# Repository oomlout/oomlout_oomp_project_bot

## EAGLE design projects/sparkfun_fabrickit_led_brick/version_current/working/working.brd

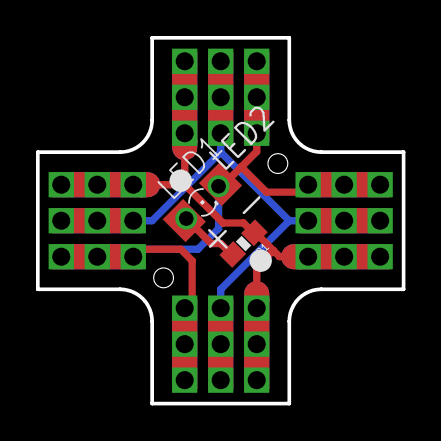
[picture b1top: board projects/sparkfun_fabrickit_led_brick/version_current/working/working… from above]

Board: 2 copper layers, 20.3 x 20.3 mm, 8 parts (0 on the bottom side), 4 nets.

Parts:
J1, J2: FKIT-RIBBON_CONNECTOR-2MM_L_REV2; FKIT-RIBBON_CONNECTOR_03_2MM_L
J3, J4: FKIT-RIBBON_CONNECTOR-2MM_R_REV2; FKIT-RIBBON_CONNECTOR_03_2MM_R
LED1: FKIT-LED-1206_NO_CREAM
LED2: LED3MM-NS
R1: 0603-RES
U$1: CREATIVE_COMMONS

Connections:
5V: J1.P1A, J2.P1A, J3.P1A, J4.P1A, R1.1
GND: J1.P3A, J2.P3A, J3.P3A, J4.P3A, LED1.C, LED2.K
unnamed: J1.P2A, J2.P2A, J3.P2A, J4.P2A
unnamed: LED1.A, LED2.A, R1.2

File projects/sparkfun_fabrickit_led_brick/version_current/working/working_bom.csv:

Row,Description,Part,References,Value,Footprint,Quantity Per PCB,Status,Datasheet
1,,FKIT-RIBBON_CONNECTOR-2MM_L_REV2,J1 J2,FKIT-RIBBON_CONNECTOR-2MM_L_REV2,FKIT-RIBBON_CONNECTOR_03_2MM_L,2, ,
2,,FKIT-RIBBON_CONNECTOR-2MM_R_REV2,J3 J4,FKIT-RIBBON_CONNECTOR-2MM_R_REV2,FKIT-RIBBON_CONNECTOR_03_2MM_R,2, ,
3,,LED,LED1,LED,FKIT-LED-1206_NO_CREAM,1, ,
4,,LED-3MM-NO_SILK,LED2,LED-3MM-NO_SILK,LED3MM-NS,1, ,
5,,RESISTOR0603,R1,RESISTOR0603,0603-RES,1, ,
6,,CREATIVE_COMMONS,U$1,CREATIVE_COMMONS,CREATIVE_COMMONS,1, ,





Project info:
Schematic:,working
Variant:,default
Revision:,
Date:,2023-08-06_12-56-02
KiCad Version:,7.0.6-7.0.6~ubuntu22.04.1
Statistics:
Component Groups:,6
Component Count:,8 (0 SMD/ 0 THT)
Fitted Components:,8 (0 SMD/ 0 THT)
Number of PCBs:,1
Total Components:,8

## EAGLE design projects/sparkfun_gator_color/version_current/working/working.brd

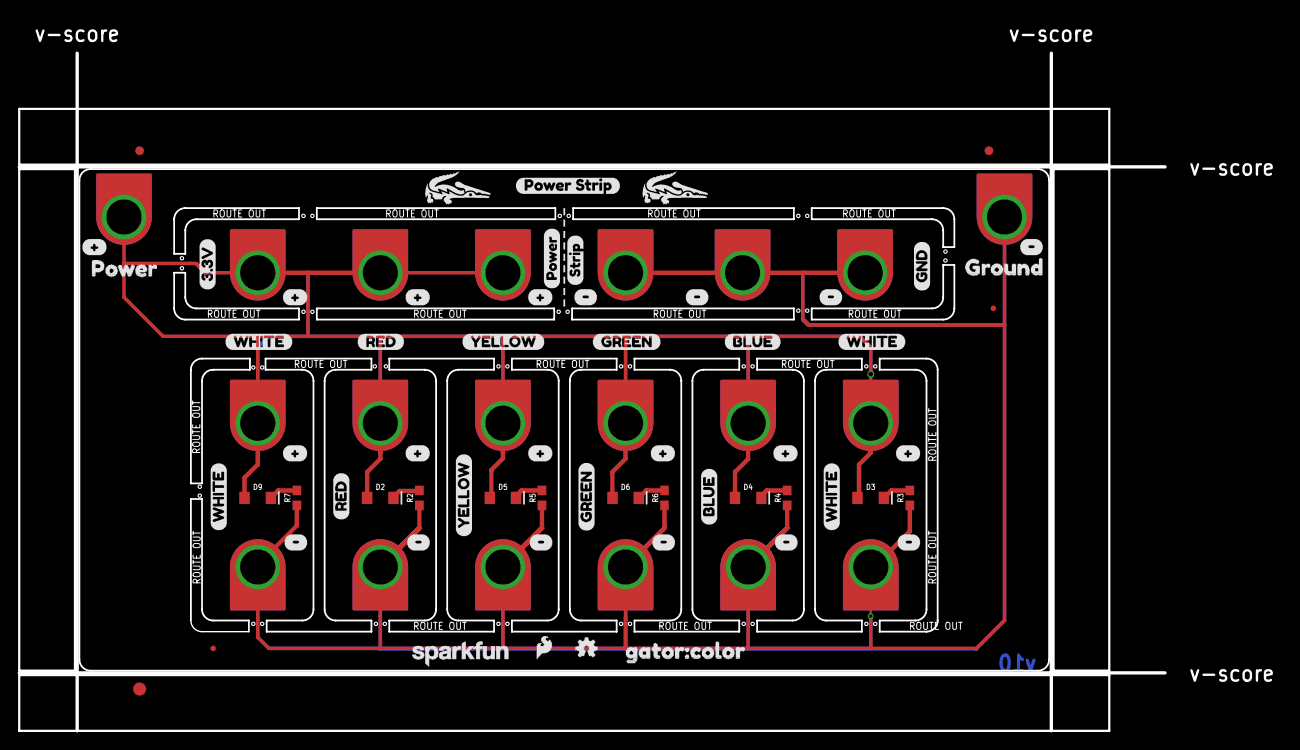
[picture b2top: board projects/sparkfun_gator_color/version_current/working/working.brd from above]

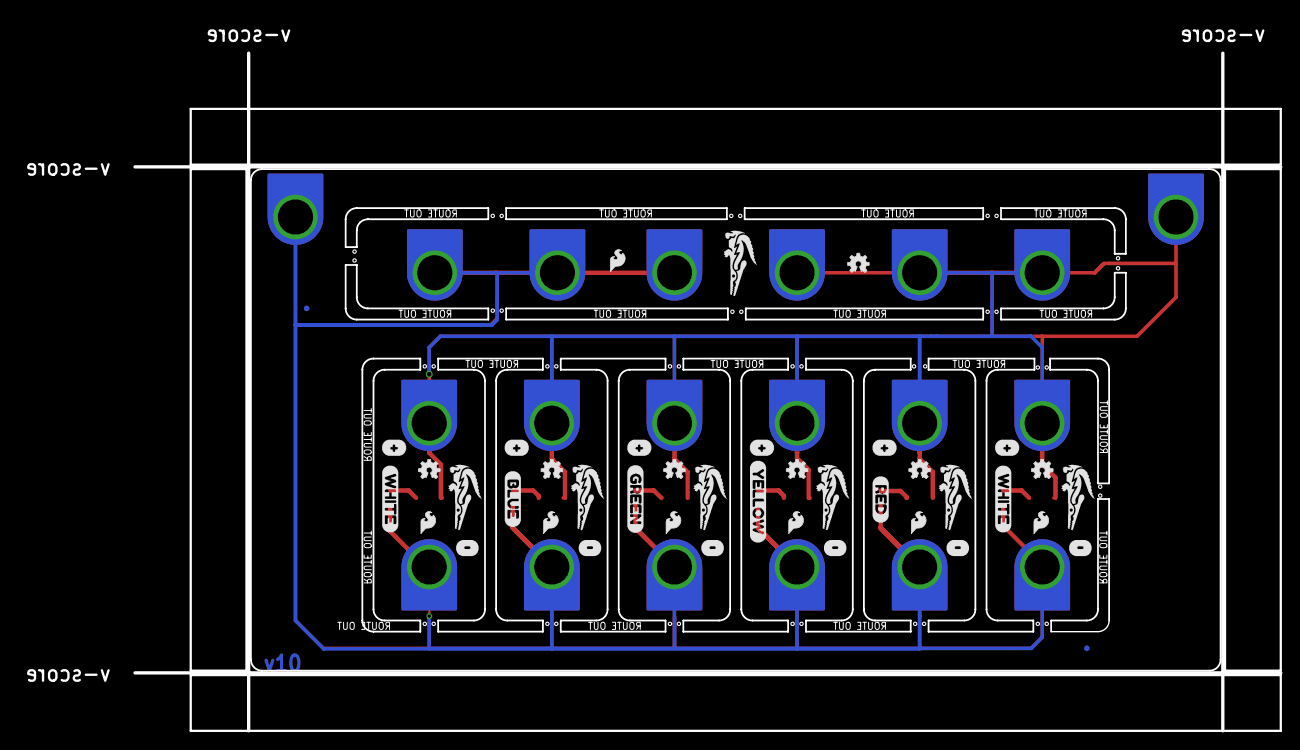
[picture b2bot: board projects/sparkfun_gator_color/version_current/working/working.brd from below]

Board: 2 copper layers, 130.6 x 77.2 mm, 123 parts (41 on the bottom side), 8 nets.

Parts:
D2: RED; LED-1206
D3, D9: WHITE; LED-1206
D4: BLUE; LED-1206
D5: Yellow; LED-1206
D6: GREEN; LED-1206
E$1, E$2: FIDUCIAL-1X2
E$3: FIDUCIAL-1.5X3
FD1, FD2, FD3, FD4: FIDUCIALUFIDUCIAL; FIDUCIAL-MICRO
LOGO1, LOGO9, LOGO10, LOGO11, LOGO12, LOGO13, LOGO17, LOGO19: SFE_LOGO_FLAME.1_INCH; SFE_LOGO_FLAME_.1
LOGO2, LOGO3, LOGO4, LOGO5, LOGO6, LOGO7, LOGO15, LOGO18: OSHW-LOGOMINI; OSHW-LOGO-MINI
LOGO16: SFE_LOGO_NAME.1_INCH; SFE_LOGO_NAME_.1
R2, R3, R5, R7: 330; 0603
R4, R6: 150; 0603
U$1, U$2, U$3, U$6, U$7, U$8, U$10, U$11, U$13, U$16, U$18, U$19, U$20, U$21, U$28, U$30, U$32, U$33, U$34, U$38: TAB_GATOR_MINI
U$5: POWER_STRIP0
U$9: GROUND3
U$12, U$14, U$15, U$53, U$55, U$57, U$60, U$62, U$64, U$77, U$81, U$83, U$84, U$85, U$86, U$87: #8
U$17, U$41, U$42: RED2
U$22, U$23, U$24, U$54, U$56, U$58, U$61, U$63, U$65, U$82, U$89, U$90, U$91, U$92, U$93, U$95: #9
U$25: 3#3V1
U$26: GND0
U$27: POWER1
U$29, U$31, U$50, U$68, U$69, U$70, U$71, U$72, U$73: GATOR#PNG
U$35: STRIP2
U$36, U$37, U$75: BLUE4
U$39, U$40, U$67: GREEN3
U$43: POWER2
U$44, U$45, U$46, U$47, U$78, U$79: WHITE6
U$48, U$49, U$76: YELLOW5
U$51: GATOR#COLOR0

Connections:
3.3V: D2.A, D3.A, D4.A, D5.A, D6.A, D9.A, U$10.P1, U$13.P1, U$16.P1, U$18.P1, U$19.P1, U$20.P1, U$21.P1, U$32.P1, U$33.P1, U$34.P1
GND: R2.1, R3.1, R4.1, R5.1, R6.1, R7.1, U$1.P1, U$2.P1, U$3.P1, U$6.P1, U$7.P1, U$8.P1, U$11.P1, U$28.P1, U$30.P1, U$38.P1
unnamed: D2.C, R2.2
unnamed: D3.C, R3.2
unnamed: D4.C, R4.2
unnamed: D5.C, R5.2
unnamed: D6.C, R6.2
unnamed: D9.C, R7.2

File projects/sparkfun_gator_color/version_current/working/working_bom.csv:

Row,Description,Part,References,Value,Footprint,Quantity Per PCB,Status,Datasheet
1,,LED-BLUE1206,D4,BLUE,LED-1206,1, ,
2,,LED-GREEN1206,D6,GREEN,LED-1206,1, ,
3,,LED-RED1206,D2,RED,LED-1206,1, ,
4,,LED-WHITE1206,D3 D9,WHITE,LED-1206,2, ,
5,,LED-YELLOWLILYPAD,D5,Yellow,LED-1206,1, ,
6,,FRAME-LETTER,FRAME1,FRAME-LETTER,CREATIVE_COMMONS,1, ,
7,,OSHW-LOGOMINI,LOGO2 LOGO15,OSHW-LOGOMINI,OSHW-LOGO-MINI,2, ,
8,,REVISION,LOGO8,REVISION,REVISION,1, ,
9,,SFE_LOGO_FLAME.1_INCH,LOGO1,SFE_LOGO_FLAME.1_INCH,SFE_LOGO_FLAME_.1,1, ,
10,,SFE_LOGO_NAME.1_INCH,LOGO16,SFE_LOGO_NAME.1_INCH,SFE_LOGO_NAME_.1,1, ,
11,,150OHM-0603-1/10W-1%,R4 R6,150OHM-0603-1/10W-1%,0603,2, ,
12,,330OHM-0603-1/10W-1%,R2 R3 R5 R7,330OHM-0603-1/10W-1%,0603,4, ,
13,,TAB_GATOR_MINI,U$1 U$2 U$3 U$6 U$7 U$8 U$10 U$11 U$13 U$16 U$18 U$19 U$20 U$21 U$28 U$30 U$32 U$33 U$34 U$38,TAB_GATOR_MINI,TAB_GATOR_MINI,20, ,





Project info:
Schematic:,working
Variant:,default
Revision:,
Date:,2023-08-06_12-56-02
KiCad Version:,7.0.6-7.0.6~ubuntu22.04.1
Statistics:
Component Groups:,13
Component Count:,38 (0 SMD/ 0 THT)
Fitted Components:,38 (0 SMD/ 0 THT)
Number of PCBs:,1
Total Components:,38

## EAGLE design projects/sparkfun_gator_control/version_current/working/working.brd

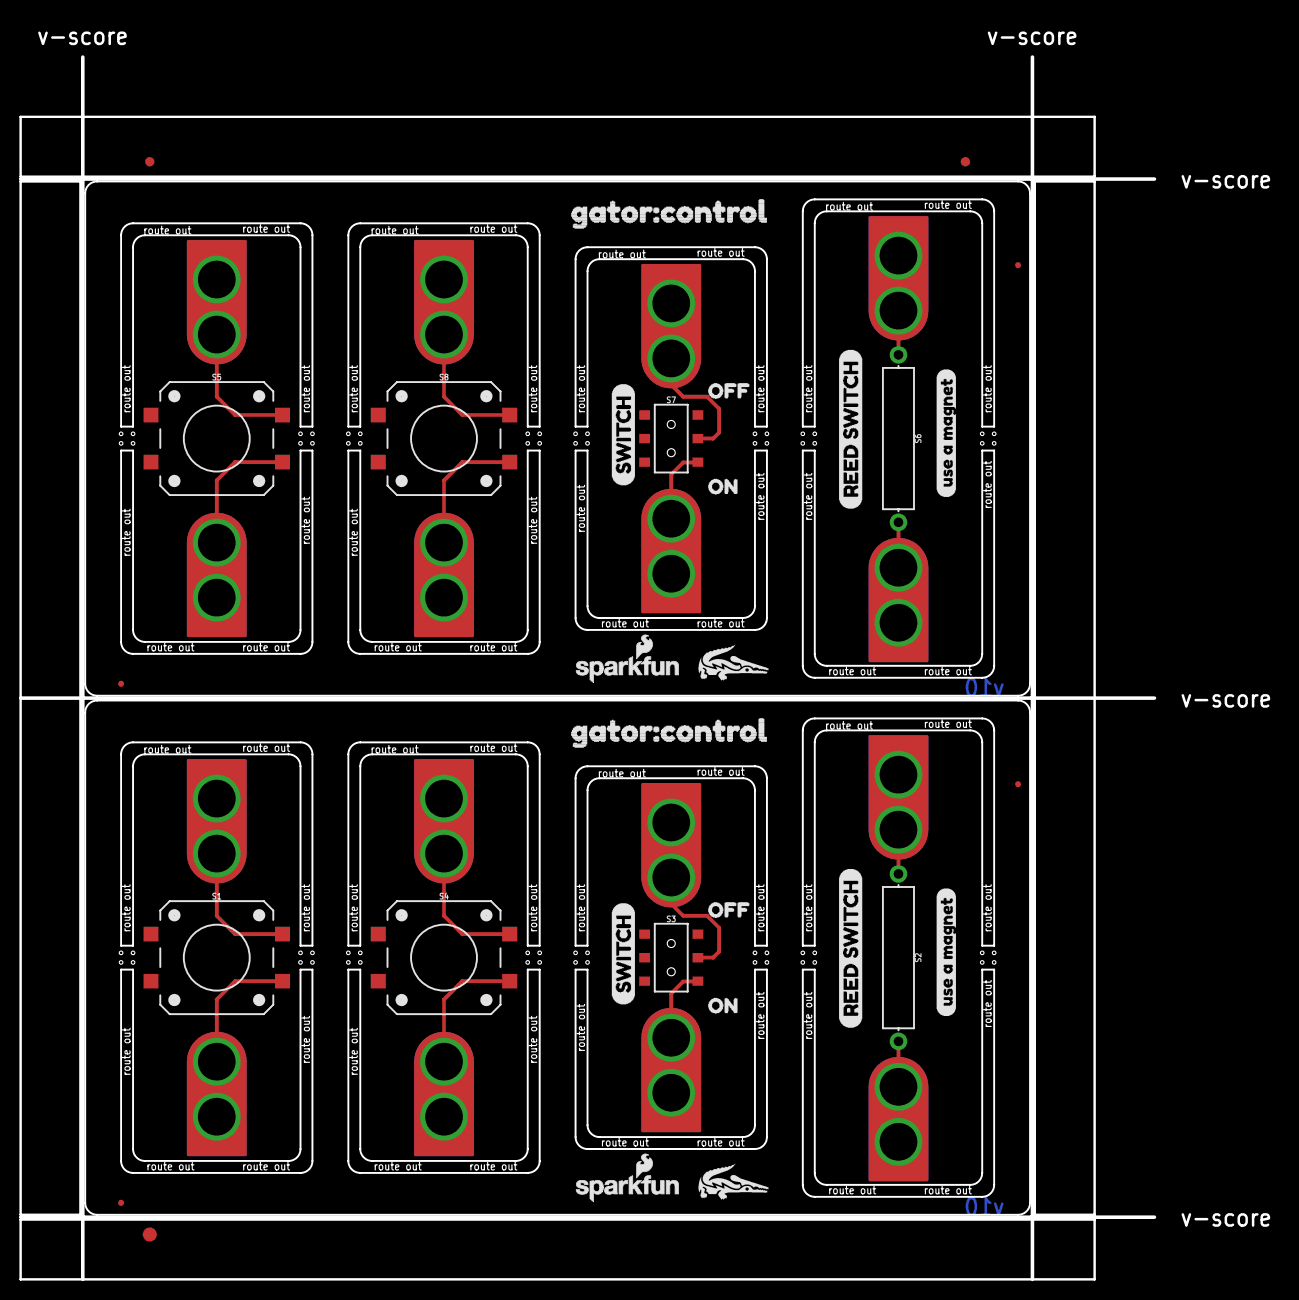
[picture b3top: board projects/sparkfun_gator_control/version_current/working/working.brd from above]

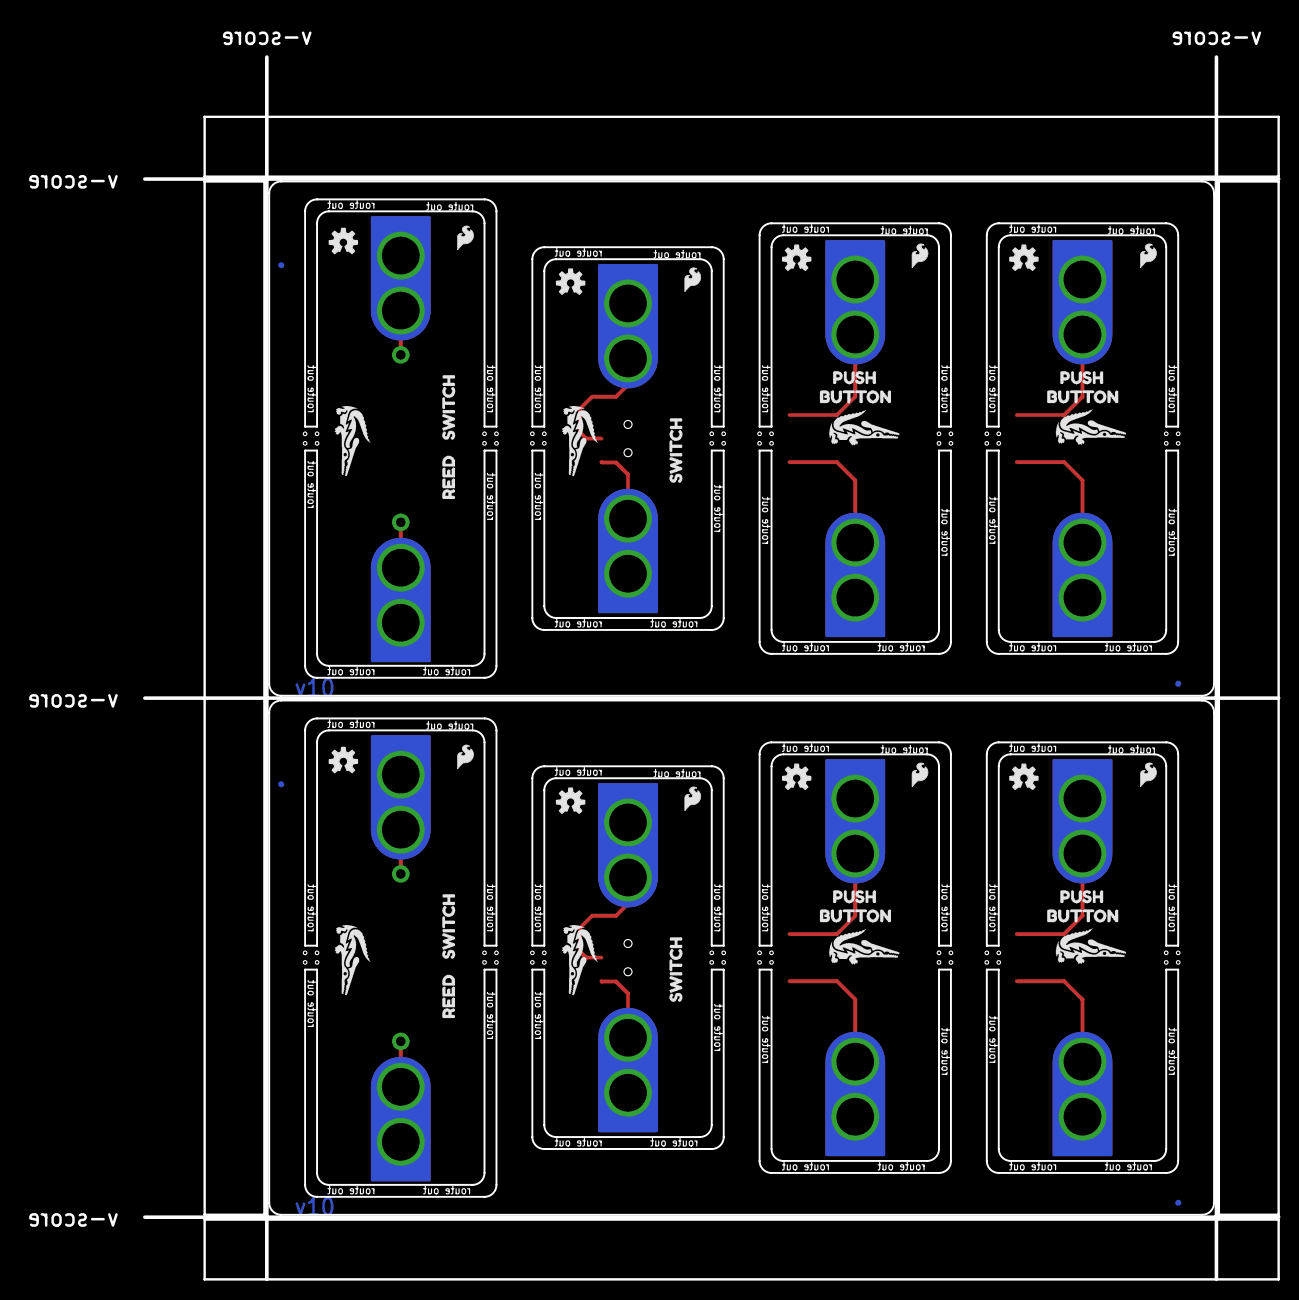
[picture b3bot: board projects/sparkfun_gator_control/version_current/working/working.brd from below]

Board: 2 copper layers, 120.4 x 129.8 mm, 89 parts (42 on the bottom side), 16 nets.

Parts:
E$1, E$2: FIDUCIAL-1X2
E$3: FIDUCIAL-1.5X3
FD1, FD2, FD3, FD4, FD5, FD6, FD7, FD8: FIDUCIALUFIDUCIAL; FIDUCIAL-MICRO
LOGO1, LOGO4, LOGO6, LOGO7, LOGO9, LOGO12, LOGO14, LOGO15: SFE_LOGO_FLAME.1_INCH; SFE_LOGO_FLAME_.1
LOGO2, LOGO3, LOGO5, LOGO8, LOGO10, LOGO11, LOGO13, LOGO16: OSHW-LOGOS; OSHW-LOGO-S
S1, S4, S5, S8: MOMENTARY-SWITCH-SPST-SMD-12MM; TACTILE_SWITCH_SMD_12MM
S2, S6: REED_SWITCH-PTH-INSULATED; REED_SWITCH_PLASTIC
S3, S7: SWITCH_DPDT_SMD_AYZ0202
U$1, U$22, U$25, U$26, U$27, U$28, U$29, U$38, U$51, U$70: GATOR#PNG
U$2, U$5, U$39, U$42: BUTTON3
U$3, U$4, U$40, U$41: PUSH4
U$6, U$46: OFF9
U$7, U$43: REED_SWITCH0
U$8, U$44: SWITCH2
U$9, U$45: USE_A_MAGNET10
U$10, U$11, U$12, U$14, U$15, U$16, U$17, U$19, U$30, U$31, U$32, U$33, U$34, U$35, U$36, U$37: GATOR
U$13, U$47: ON8
U$18, U$21, U$48, U$50: SWITCH5
U$20, U$49: REED6
U$23, U$52: GATOR#CONTROL0
U$24, U$53: SFE_LOGO_NAME_FLAME_.1

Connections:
unnamed: S4.1, U$19.P$1, U$19.P$2
unnamed: S4.3, U$10.P$1, U$10.P$2
unnamed: S1.1, U$17.P$1, U$17.P$2
unnamed: S1.3, U$11.P$1, U$11.P$2
unnamed: S2.P$1, U$16.P$1, U$16.P$2
unnamed: S2.P$2, U$12.P$1, U$12.P$2
unnamed: S3.2, U$15.P$1, U$15.P$2
unnamed: S3.3, U$14.P$1, U$14.P$2
unnamed: S8.1, U$37.P$1, U$37.P$2
unnamed: S8.3, U$30.P$1, U$30.P$2
unnamed: S5.1, U$36.P$1, U$36.P$2
unnamed: S5.3, U$31.P$1, U$31.P$2
unnamed: S6.P$1, U$35.P$1, U$35.P$2
unnamed: S6.P$2, U$32.P$1, U$32.P$2
unnamed: S7.2, U$34.P$1, U$34.P$2
unnamed: S7.3, U$33.P$1, U$33.P$2

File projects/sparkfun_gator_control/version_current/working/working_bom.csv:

Row,Description,Part,References,Value,Footprint,Quantity Per PCB,Status,Datasheet
1,,FRAME-LETTER,FRAME1,FRAME-LETTER,CREATIVE_COMMONS,1, ,
2,,OSHW-LOGOS,LOGO2,OSHW-LOGOS,OSHW-LOGO-S,1, ,
3,,REVISION,LOGO9,REVISION,REVISION,1, ,
4,,SFE_LOGO_FLAME.1_INCH,LOGO1,SFE_LOGO_FLAME.1_INCH,SFE_LOGO_FLAME_.1,1, ,
5,,MOMENTARY-SWITCH-SPST-SMD-12MM,S1 S4,MOMENTARY-SWITCH-SPST-SMD-12MM,TACTILE_SWITCH_SMD_12MM,2, ,
6,,REED_SWITCH-PTH-INSULATED,S2,REED_SWITCH-PTH-INSULATED,REED_SWITCH_PLASTIC,1, ,
7,,SWITCH-SPDT-SMD-AYZ0202,S3,SWITCH-SPDT-SMD-AYZ0202,SWITCH_DPDT_SMD_AYZ0202,1, ,
8,,GATOR,U$10 U$11 U$12 U$14 U$15 U$16 U$17 U$19,GATOR,GATOR,8, ,





Project info:
Schematic:,working
Variant:,default
Revision:,
Date:,2023-08-06_12-56-02
KiCad Version:,7.0.6-7.0.6~ubuntu22.04.1
Statistics:
Component Groups:,8
Component Count:,16 (0 SMD/ 0 THT)
Fitted Components:,16 (0 SMD/ 0 THT)
Number of PCBs:,1
Total Components:,16

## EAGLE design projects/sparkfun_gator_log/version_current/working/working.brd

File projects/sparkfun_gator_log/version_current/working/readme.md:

# OOMP Project  
## gator_log  by sparkfun  
  
oomp key: oomp_projects_flat_sparkfun_gator_log  
(snippet of original readme)  
  
SparkFun gator:log - micro:bit Accessory Board  
========================================  

[*SparkFun gator:log - micro:bit Accessory Board (DEV-15270)*](https://www.sparkfun.com/products/15270)  
  
The gator:log is the perfect data logging tool for your next experiment. With the automation of the data collection process, gone are the days of rushing around with a pen and composition notebook to simultaneously record data and your observations. The gator:log allows a student(s) to focus more on what is happening in the experiment than watching a thermometer or sensor readout.  
  
Instead of using pin connections or requiring soldering, this product provides connection pads for a more kid freindly experience with alligator clips. The design intention of this product is to be used with the [gato:bit (v2)](https://www.sparkfun.com/products/15162), and the [micro:bit development board](https://www.sparkfun.com/products/14208).  
  
Repository Contents  
-------------------  
  
* **/Firmware/Qwiic_OpenLog** - The core sketch that runs Qwiic OpenLog  
* **/Hardware** - Eagle design files (.brd, .sch)  
  
Documentation  
--------------  
  
* **[Hookup Guide](https://learn.sparkfun.com/tutorials/sparkfun-gatorlog-hookup-guide)** - Basic hookup guide for the gator:log.  
* **[gator:RTC PXT Package](https://github.com/sparkfun/pxt-gator-log)** - PXT- packa  
  full source readme at [readme_src.md](readme_src.md)  
  
source repo at: [https://github.com/sparkfun/gator_log](https://github.com/sparkfun/gator_log)  
## Board  

## Schematic  

[schematic pdf](working_schematic.pdf)  
## Images

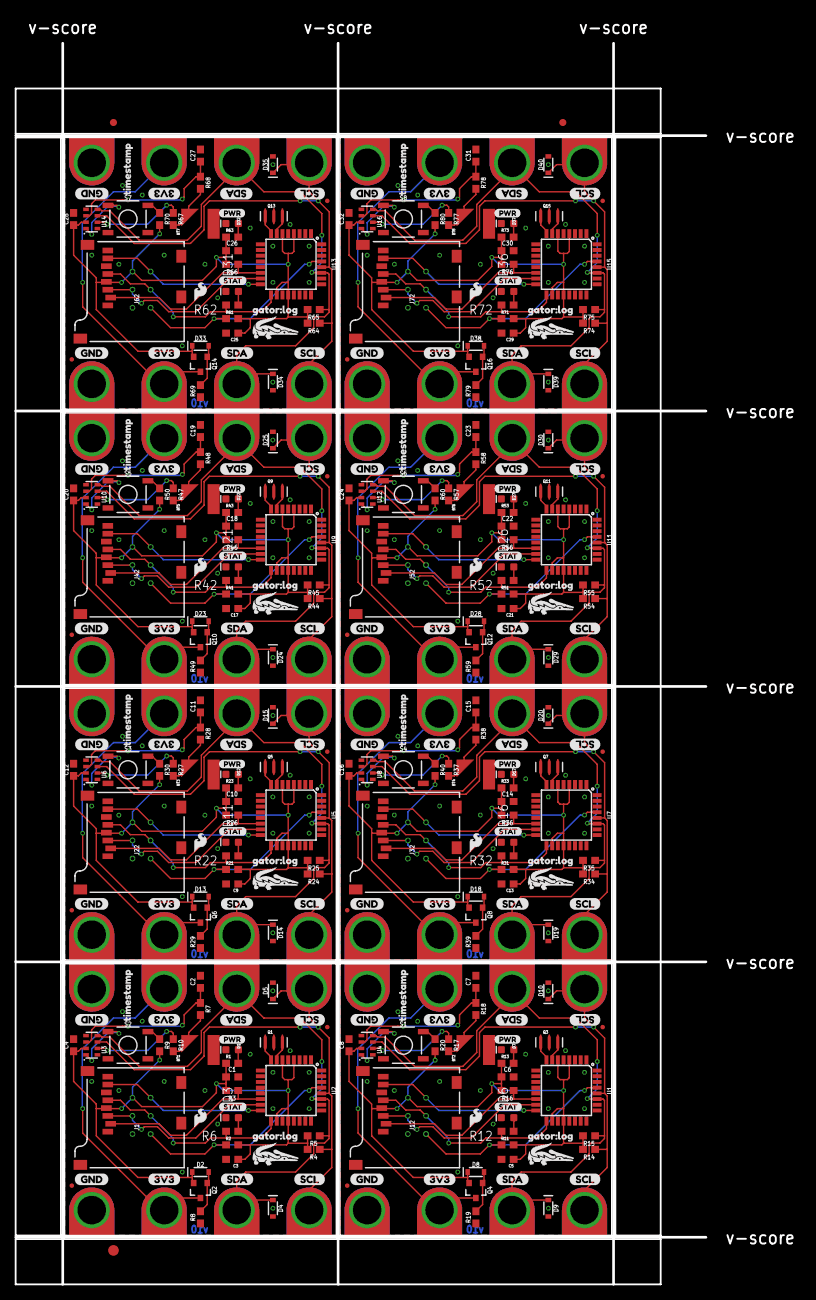
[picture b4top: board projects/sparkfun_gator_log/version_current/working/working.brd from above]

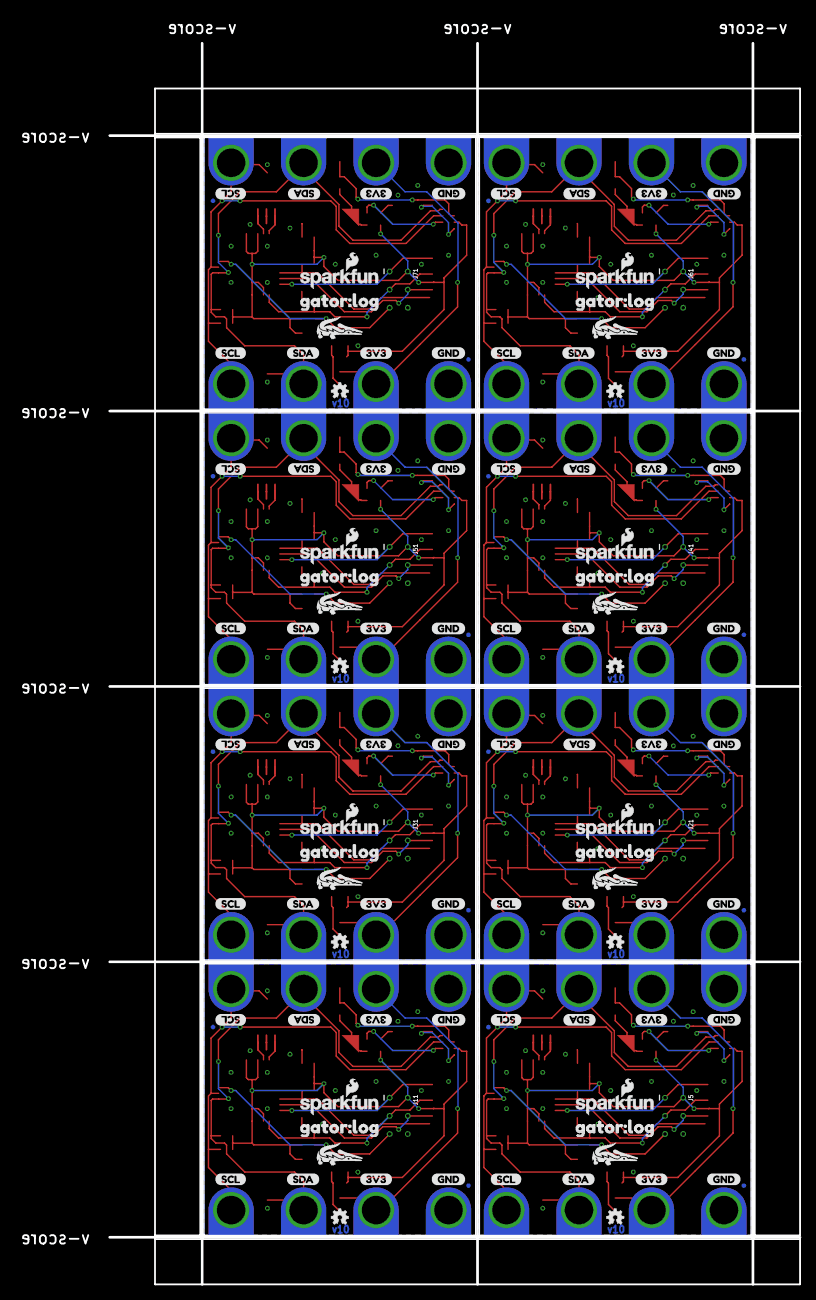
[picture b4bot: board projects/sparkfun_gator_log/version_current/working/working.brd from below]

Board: 2 copper layers, 96.8 x 174.0 mm, 523 parts (120 on the bottom side), 152 nets.

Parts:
BT1, BT2, BT3, BT4, BT5, BT6, BT7, BT8: ML414H_IV01E_BATTERY; ML414H_IV01E
C1, C6, C10, C14, C18, C22, C26, C30: 4.7uF; 0603
C2, C3, C4, C5, C7, C8, C9, C11, C12, C13, C15, C16, C17, C19, C20, C21, C23, C24, C25, C27, C28, C29, C31, C32: 0.1uF; 0603
D1, D7, D12, D17, D22, D27, D32, D37: RED; LED-0603
D2, D4, D5, D8, D9, D10, D13, D14, D15, D18, D19, D20, D23, D24, D25, D28, D29, D30, D33, D34, D35, D38, D39, D40: 3.6V; SOD-323
D3, D6, D11, D16, D21, D26, D31, D36: GREEN; LED-0603
E$1, E$2: FIDUCIAL-1X2
E$3: FIDUCIAL-1.5X3
FID1, FID2, FID3, FID4, FID5, FID6, FID7, FID8, FID9, FID10, FID11, FID12, FID13, FID14, FID15, FID16, FID17, FID18, FID19, FID20, FID21, FID22, FID23, FID24, FID25, FID26, FID27, FID28, FID29, FID30, FID31, FID32: FIDUCIALUFIDUCIAL; FIDUCIAL-MICRO
J1, J12, J22, J32, J42, J52, J62, J72: MICRO-SD; MICRO-SD-SOCKET
J2, J3, J4, J6, J7, J8, J9, J10, J13, J14, J15, J16, J17, J18, J19, J20, J23, J24, J25, J26, J27, J28, J29, J30, J33, J34, J35, J36, J37, J38, J39, J40, J43, J44, J45, J46, J47, J48, J49, J50, J53, J54, J55, J56, J57, J58, J59, J60, J63, J64, J65, J66, J67, J68, J69, J70, J73, J74, J75, J76, J77, J78, J79, J80: GATORGATOR_MINI; GATOR_MINI
J5, J11, J21, J31, J41, J51, J61, J71: ISP; 2X3_TEST_POINTS
LOGO1, LOGO6, LOGO9, LOGO12, LOGO15, LOGO18, LOGO21, LOGO24: SFE_LOGO_FLAME.1_INCH; SFE_LOGO_FLAME_.1
LOGO2, LOGO3, LOGO7, LOGO10, LOGO13, LOGO16, LOGO19, LOGO22: OSHW-LOGOMINI; OSHW-LOGO-MINI
LOGO4, LOGO5, LOGO8, LOGO11, LOGO14, LOGO17, LOGO20, LOGO23: SFE_LOGO_NAME_FLAME.1_INCH; SFE_LOGO_NAME_FLAME_.1
Q1, Q3, Q5, Q7, Q9, Q11, Q13, Q15: 16MHZ; RESONATOR-SMD
Q2, Q4, Q6, Q8, Q10, Q12, Q14, Q16: 2.5A/30V/105mΩ; SOT23-3
R1, R13, R23, R33, R43, R53, R63, R73: 1k; 0603
R2, R3, R4, R5, R8, R9, R10, R11, R14, R15, R16, R17, R19, R20, R21, R24, R25, R26, R27, R29, R30, R31, R34, R35, R36, R37, R39, R40, R41, R44, R45, R46, R47, R49, R50, R51, R54, R55, R56, R57, R59, R60, R61, R64, R65, R66, R67, R69, R70, R71, R74, R75, R76, R77, R79, R80: 10k; 0603
R6, R12, R22, R32, R42, R52, R62, R72: 330; 0603
R7, R18, R28, R38, R48, R58, R68, R78: 470; 0603
S1, S2, S3, S4, S5, S6, S7, S8: TACTILE_SWITCH_SMD_5.2MM
U1, U2, U5, U7, U9, U11, U13, U15: ATMEGA328P; TQFP32-08
U3, U4, U6, U8, U10, U12, U14, U16: RV-3028
U$1, U$3, U$12, U$15, U$26, U$28, U$35, U$38, U$49, U$51, U$58, U$61, U$72, U$74, U$81, U$84, U$95, U$97, U$104, U$107, U$118, U$120, U$127, U$130, U$141, U$143, U$150, U$153, U$164, U$166, U$173, U$176: 3V33
U$2, U$10, U$11, U$23, U$27, U$33, U$34, U$44, U$50, U$56, U$57, U$67, U$73, U$79, U$80, U$90, U$96, U$102, U$103, U$113, U$119, U$125, U$126, U$136, U$142, U$148, U$149, U$159, U$165, U$171, U$172, U$182: GND0
U$4, U$7, U$13, U$16, U$29, U$32, U$36, U$39, U$52, U$55, U$59, U$62, U$75, U$78, U$82, U$85, U$98, U$101, U$105, U$108, U$121, U$124, U$128, U$131, U$144, U$147, U$151, U$154, U$167, U$170, U$174, U$177: SDA1
U$5, U$6, U$14, U$18, U$30, U$31, U$37, U$40, U$53, U$54, U$60, U$63, U$76, U$77, U$83, U$86, U$99, U$100, U$106, U$109, U$122, U$123, U$129, U$132, U$145, U$146, U$152, U$155, U$168, U$169, U$175, U$178: SCL2
U$8, U$21, U$41, U$43, U$64, U$66, U$87, U$89, U$110, U$112, U$133, U$135, U$156, U$158, U$179, U$181: GATORBIT_FINAL_FOR_SILK#01#PNG
U$9, U$22, U$47, U$70, U$93, U$116, U$139, U$162: PWR-()-03
U$17, U$25, U$48, U$71, U$94, U$117, U$140, U$163: STAT0
U$19, U$46, U$69, U$92, U$115, U$138, U$161, U$184: TIMESTAMP0
U$20, U$42, U$65, U$88, U$111, U$134, U$157, U$180: GATOR#LOG3
U$24, U$45, U$68, U$91, U$114, U$137, U$160, U$183: GATOR#LOG0

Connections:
3.3V: C1.1, C3.1, C4.1, D2.C, J1.VCC, J5.2, Q2.2, R1.1, R2.2, R3.2, R4.2, R5.2, R9.2, U2.4, U2.6, U2.18, U2.20, U3.7
3.3V1: C5.1, C6.1, C8.1, D8.C, J11.2, J12.VCC, Q4.2, R11.2, R13.1, R14.2, R15.2, R16.2, R20.2, U1.4, U1.6, U1.18, U1.20, U4.7
3.3V2: C9.1, C10.1, C12.1, D13.C, J21.2, J22.VCC, Q6.2, R21.2, R23.1, R24.2, R25.2, R26.2, R30.2, U5.4, U5.6, U5.18, U5.20, U6.7
3.3V3: C13.1, C14.1, C16.1, D18.C, J31.2, J32.VCC, Q8.2, R31.2, R33.1, R34.2, R35.2, R36.2, R40.2, U7.4, U7.6, U7.18, U7.20, U8.7
3.3V4: C17.1, C18.1, C20.1, D23.C, J41.2, J42.VCC, Q10.2, R41.2, R43.1, R44.2, R45.2, R46.2, R50.2, U9.4, U9.6, U9.18, U9.20, U10.7
3.3V5: C21.1, C22.1, C24.1, D28.C, J51.2, J52.VCC, Q12.2, R51.2, R53.1, R54.2, R55.2, R56.2, R60.2, U11.4, U11.6, U11.18, U11.20, U12.7
3.3V6: C25.1, C26.1, C28.1, D33.C, J61.2, J62.VCC, Q14.2, R61.2, R63.1, R64.2, R65.2, R66.2, R70.2, U13.4, U13.6, U13.18, U13.20, U14.7
3.3V7: C29.1, C30.1, C32.1, D38.C, J71.2, J72.VCC, Q16.2, R71.2, R73.1, R74.2, R75.2, R76.2, R80.2, U15.4, U15.6, U15.18, U15.20, U16.7
!RST: R10.1, U3.2
!RST1: R17.1, U4.2
!RST2: R27.1, U6.2
!RST3: R37.1, U8.2
!RST4: R47.1, U10.2
!RST5: R57.1, U12.2
!RST6: R67.1, U14.2
!RST7: R77.1, U16.2
CS: J1.CS, R3.1, U2.14
CS1: J12.CS, R16.1, U1.14
CS2: J22.CS, R26.1, U5.14
CS3: J32.CS, R36.1, U7.14
CS4: J42.CS, R46.1, U9.14
CS5: J52.CS, R56.1, U11.14
CS6: J62.CS, R66.1, U13.14
CS7: J72.CS, R76.1, U15.14
GND: BT1.-, C1.2, C2.2, C3.2, C4.2, D1.C, D3.C, D4.A, D5.A, J1.GND, J5.6, J6.P$2, J10.P$2, Q1.2, R8.1, S2.3, S2.4, U2.3, U2.5, U2.21, U3.5
GND1: BT2.-, C5.2, C6.2, C7.2, C8.2, D6.C, D7.C, D9.A, D10.A, J11.6, J12.GND, J16.P$2, J20.P$2, Q3.2, R19.1, S1.3, S1.4, U1.3, U1.5, U1.21, U4.5
GND2: BT3.-, C9.2, C10.2, C11.2, C12.2, D11.C, D12.C, D14.A, D15.A, J21.6, J22.GND, J26.P$2, J30.P$2, Q5.2, R29.1, S3.3, S3.4, U5.3, U5.5, U5.21, U6.5
GND3: BT4.-, C13.2, C14.2, C15.2, C16.2, D16.C, D17.C, D19.A, D20.A, J31.6, J32.GND, J36.P$2, J40.P$2, Q7.2, R39.1, S4.3, S4.4, U7.3, U7.5, U7.21, U8.5
GND4: BT5.-, C17.2, C18.2, C19.2, C20.2, D21.C, D22.C, D24.A, D25.A, J41.6, J42.GND, J46.P$2, J50.P$2, Q9.2, R49.1, S5.3, S5.4, U9.3, U9.5, U9.21, U10.5
GND5: BT6.-, C21.2, C22.2, C23.2, C24.2, D26.C, D27.C, D29.A, D30.A, J51.6, J52.GND, J56.P$2, J60.P$2, Q11.2, R59.1, S6.3, S6.4, U11.3, U11.5, U11.21, U12.5
GND6: BT7.-, C25.2, C26.2, C27.2, C28.2, D31.C, D32.C, D34.A, D35.A, J61.6, J62.GND, J66.P$2, J70.P$2, Q13.2, R69.1, S7.3, S7.4, U13.3, U13.5, U13.21, U14.5
GND7: BT8.-, C29.2, C30.2, C31.2, C32.2, D36.C, D37.C, D39.A, D40.A, J71.6, J72.GND, J76.P$2, J80.P$2, Q15.2, R79.1, S8.3, S8.4, U15.3, U15.5, U15.21, U16.5
MISO: J1.DO, J5.1, U2.16
MISO1: J11.1, J12.DO, U1.16
MISO2: J21.1, J22.DO, U5.16
MISO3: J31.1, J32.DO, U7.16
MISO4: J41.1, J42.DO, U9.16
MISO5: J51.1, J52.DO, U11.16
MISO6: J61.1, J62.DO, U13.16
MISO7: J71.1, J72.DO, U15.16
MOSI: J1.DI, J5.4, U2.15
MOSI1: J11.4, J12.DI, U1.15
MOSI2: J21.4, J22.DI, U5.15
MOSI3: J31.4, J32.DI, U7.15
MOSI4: J41.4, J42.DI, U9.15
MOSI5: J51.4, J52.DI, U11.15
MOSI6: J61.4, J62.DI, U13.15
MOSI7: J71.4, J72.DI, U15.15
unnamed: Q1.1, U2.8
unnamed: Q1.3, U2.7
unnamed: D1.A, R1.2
unnamed: D6.A, R12.2
unnamed: J4.P$2, J9.P$2, Q2.3
unnamed: D2.A, Q2.1, R8.2
unnamed: D3.A, R6.2
unnamed: R9.1, S2.1, S2.2, U3.8
unnamed: Q3.1, U1.8
unnamed: Q3.3, U1.7
unnamed: D7.A, R13.2
unnamed: J15.P$2, J19.P$2, Q4.3
unnamed: D8.A, Q4.1, R19.2
unnamed: R20.1, S1.1, S1.2, U4.8
unnamed: D11.A, R22.2
unnamed: Q5.1, U5.8
unnamed: Q5.3, U5.7
unnamed: D12.A, R23.2
unnamed: J25.P$2, J29.P$2, Q6.3
unnamed: D13.A, Q6.1, R29.2
unnamed: R30.1, S3.1, S3.2, U6.8
unnamed: D16.A, R32.2
unnamed: Q7.1, U7.8
unnamed: Q7.3, U7.7
unnamed: D17.A, R33.2
unnamed: J35.P$2, J39.P$2, Q8.3
unnamed: D18.A, Q8.1, R39.2
unnamed: R40.1, S4.1, S4.2, U8.8
unnamed: D21.A, R42.2
unnamed: Q9.1, U9.8
unnamed: Q9.3, U9.7
unnamed: D22.A, R43.2
unnamed: J45.P$2, J49.P$2, Q10.3
unnamed: D23.A, Q10.1, R49.2
unnamed: R50.1, S5.1, S5.2, U10.8
unnamed: D26.A, R52.2
unnamed: Q11.1, U11.8
unnamed: Q11.3, U11.7
unnamed: D27.A, R53.2
unnamed: J55.P$2, J59.P$2, Q12.3
unnamed: D28.A, Q12.1, R59.2
unnamed: R60.1, S6.1, S6.2, U12.8
unnamed: D31.A, R62.2
unnamed: Q13.1, U13.8
unnamed: Q13.3, U13.7
unnamed: D32.A, R63.2
unnamed: J65.P$2, J69.P$2, Q14.3
unnamed: D33.A, Q14.1, R69.2
unnamed: R70.1, S7.1, S7.2, U14.8
unnamed: D36.A, R72.2
unnamed: Q15.1, U15.8
unnamed: Q15.3, U15.7
unnamed: D37.A, R73.2
unnamed: J75.P$2, J79.P$2, Q16.3
unnamed: D38.A, Q16.1, R79.2
unnamed: R80.1, S8.1, S8.2, U16.8
RST: J5.5, R2.1, U2.29
RST1: J11.5, R11.1, U1.29
RST2: J21.5, R21.1, U5.29
RST3: J31.5, R31.1, U7.29
RST4: J41.5, R41.1, U9.29
RST5: J51.5, R51.1, U11.29
RST6: J61.5, R61.1, U13.29
RST7: J71.5, R71.1, U15.29
SCK: J1.SCLK, J5.3, R6.1, U2.17
SCK1: J11.3, J12.SCLK, R12.1, U1.17
SCK2: J21.3, J22.SCLK, R22.1, U5.17
SCK3: J31.3, J32.SCLK, R32.1, U7.17
SCK4: J41.3, J42.SCLK, R42.1, U9.17
SCK5: J51.3, J52.SCLK, R52.1, U11.17
SCK6: J61.3, J62.SCLK, R62.1, U13.17
SCK7: J71.3, J72.SCLK, R72.1, U15.17
SCL: D5.C, J2.P$2, J7.P$2, R4.1, U2.28, U3.3
SCL1: D10.C, J13.P$2, J17.P$2, R14.1, U1.28, U4.3
SCL2: D15.C, J23.P$2, J27.P$2, R24.1, U5.28, U6.3
SCL3: D20.C, J33.P$2, J37.P$2, R34.1, U7.28, U8.3
SCL4: D25.C, J43.P$2, J47.P$2, R44.1, U9.28, U10.3
SCL5: D30.C, J53.P$2, J57.P$2, R54.1, U11.28, U12.3
SCL6: D35.C, J63.P$2, J67.P$2, R64.1, U13.28, U14.3
SCL7: D40.C, J73.P$2, J77.P$2, R74.1, U15.28, U16.3
SDA: D4.C, J3.P$2, J8.P$2, R5.1, U2.27, U3.4
SDA1: D9.C, J14.P$2, J18.P$2, R15.1, U1.27, U4.4
SDA2: D14.C, J24.P$2, J28.P$2, R25.1, U5.27, U6.4
SDA3: D19.C, J34.P$2, J38.P$2, R35.1, U7.27, U8.4
SDA4: D24.C, J44.P$2, J48.P$2, R45.1, U9.27, U10.4
SDA5: D29.C, J54.P$2, J58.P$2, R55.1, U11.27, U12.4
SDA6: D34.C, J64.P$2, J68.P$2, R65.1, U13.27, U14.4
SDA7: D39.C, J74.P$2, J78.P$2, R75.1, U15.27, U16.4
VBACKUP: C2.1, R7.1, U3.6
VBACKUP1: C7.1, R18.1, U4.6
VBACKUP2: C11.1, R28.1, U6.6
VBACKUP3: C15.1, R38.1, U8.6
VBACKUP4: C19.1, R48.1, U10.6
VBACKUP5: C23.1, R58.1, U12.6
VBACKUP6: C27.1, R68.1, U14.6
VBACKUP7: C31.1, R78.1, U16.6
V_BATT: BT1.+, R7.2, R10.2
V_BATT1: BT2.+, R17.2, R18.2
V_BATT2: BT3.+, R27.2, R28.2
V_BATT3: BT4.+, R37.2, R38.2
V_BATT4: BT5.+, R47.2, R48.2
V_BATT5: BT6.+, R57.2, R58.2
V_BATT6: BT7.+, R67.2, R68.2
V_BATT7: BT8.+, R77.2, R78.2

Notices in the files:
parts and their libraries:
SparkFun: Released under the Creative Commons Attribution Share-Alike 3.0 License
SparkFun: http://creativecommons.org/licenses/by-sa/3.0
SparkFun-Resistors: Licensing: CC v3.0 Share-Alike You are welcome to use this library for commercial purposes.
